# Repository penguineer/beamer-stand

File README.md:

dummyvideo
==========

YPbPr dummy video signal.

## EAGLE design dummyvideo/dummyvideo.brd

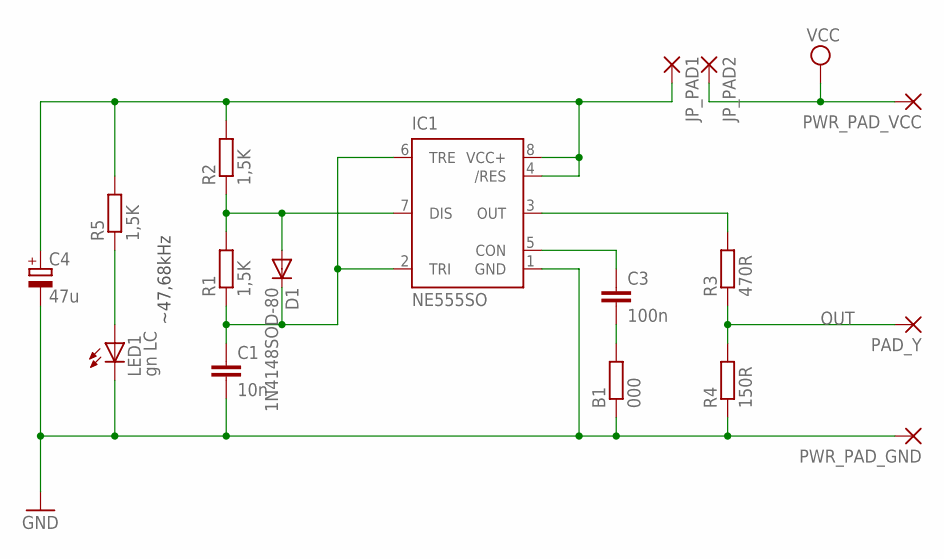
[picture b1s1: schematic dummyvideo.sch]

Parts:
B1: 000; R1206
C1: 10n; C0805
C3: 100n; C0805
C4: 47u; 153CLV-0505
D1: 1N4148SOD-80; SOD80C
IC1: NE555SO; SO08
JP_PAD1, JP_PAD2: SMD2; SMD1,27-2,54
LED1: gn LC; CHIP-LED0603
PAD_Y: SMD2; SMD1,27-2,54
PWR_PAD_GND: SMD2; SMD1,27-2,54
PWR_PAD_VCC: SMD2; SMD1,27-2,54
R1, R5: 1,5K; R0805
R2: 1,5K; M0805
R3: 470R; R0805
R4: 150R; R0805

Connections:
GND: B1.1, B1.2, C1.2, C3.2, C4.-, IC1.1 (GND), LED1.C, PWR_PAD_GND.1, R4.1
unnamed: D1.A, IC1.7 (DIS), R1.2, R2.1
unnamed: C3.1, IC1.5 (CON)
unnamed: C1.1, D1.C, IC1.2 (TRI), IC1.6 (TRE), R1.1
unnamed: IC1.3 (OUT), R3.2
unnamed: LED1.A, R5.1
OUT: PAD_Y.1, R3.1, R4.2
VCC: JP_PAD2.1, PWR_PAD_VCC.1
VCC_SW: C4.+, IC1.4 (/RES), IC1.8 (VCC+), JP_PAD1.1, R2.2, R5.2

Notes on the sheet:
~47,68kHz

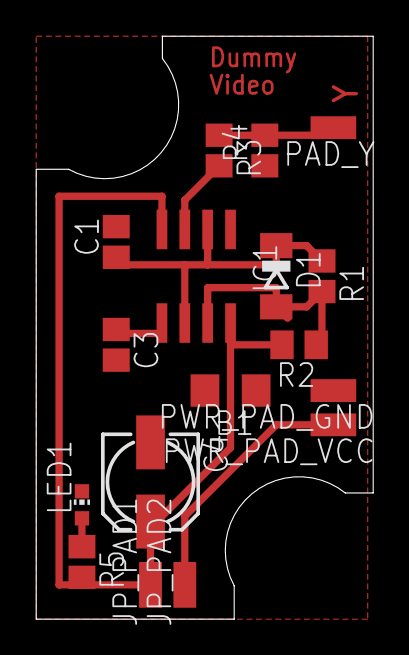
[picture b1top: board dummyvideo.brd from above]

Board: 2 copper layers, 18.7 x 32.4 mm, 17 parts (0 on the bottom side), 9 nets.

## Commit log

2014-02-17 Schematics für Dummy-Video-Schaltung
2014-02-17 Gitignore für tmp-Schematics
2014-02-17 Betriebs-LED eingefügt und Package des Ladekondensators
2014-02-17 erstes Board-Layout
2014-03-02 Added power and mount holes.
2014-04-18 Wiederstand vor der LED angepasst
2014-04-21 First revision of SMD board
2014-04-21 Scaled dimensions to 1 inch metric and added converter program
2014-04-21 Changed layout to SMD variant.
2014-04-21 PCB dimensions as DXF
2014-04-21 Correct dimensions
2014-04-21 Final Board revision
2014-04-22 Dimensions zurückskaliert
2014-05-08 Spannungsteiler war zu hochohmig -> angepasst
2014-05-10 Added pictures for documentation.
2014-06-14 Added the dummyvideo project in dummyvideo sub-folder.
2014-06-14 did not see .gitignore when moving the files …
2014-06-24 erster Entwurf Seitenwand
2014-06-25 Maße angepasst
2014-06-25 Ausschnitt und Löcher
2014-06-25 Ausschnitte und Löcher der linken Seitenwand
2014-06-25 Ausschnitt für Beamer-Unterseite
2014-06-25 Materialstärke angepasst
2014-06-25 Ausschnitte für Abstandshalter auf 15mm angepasst
2014-06-25 Orientation für DXF-Export angepasst
2014-06-25 Korrigierte DXF-Exporte
2014-06-25 Ausschnitt auf Beamerstütze links korrigiert
2014-08-16 Clip für den Kabelkanal
